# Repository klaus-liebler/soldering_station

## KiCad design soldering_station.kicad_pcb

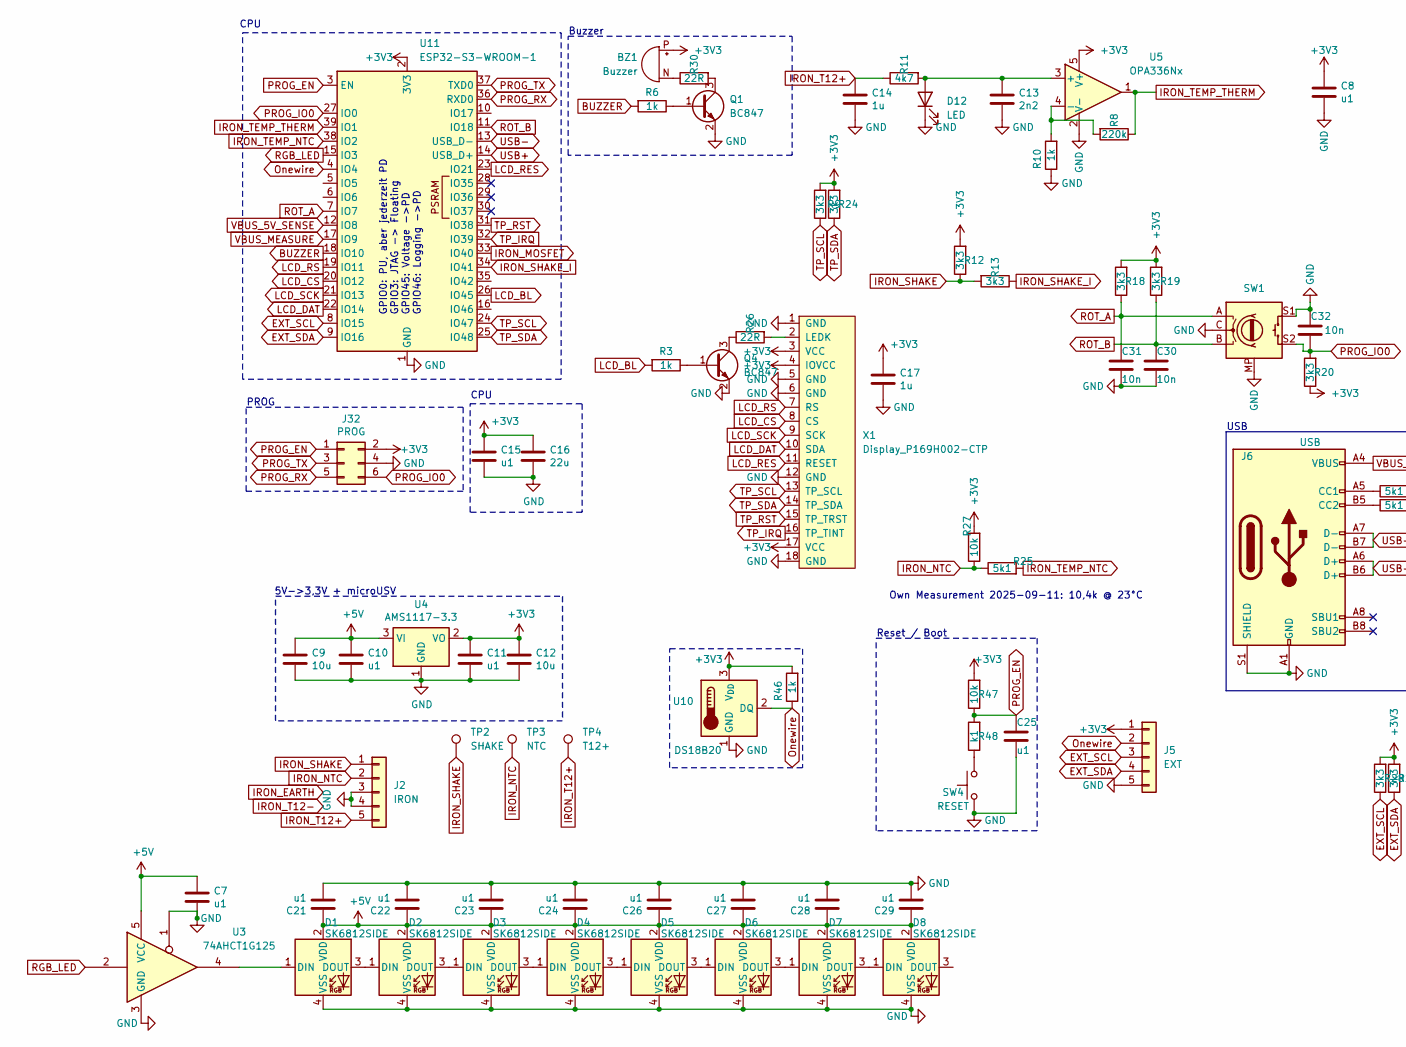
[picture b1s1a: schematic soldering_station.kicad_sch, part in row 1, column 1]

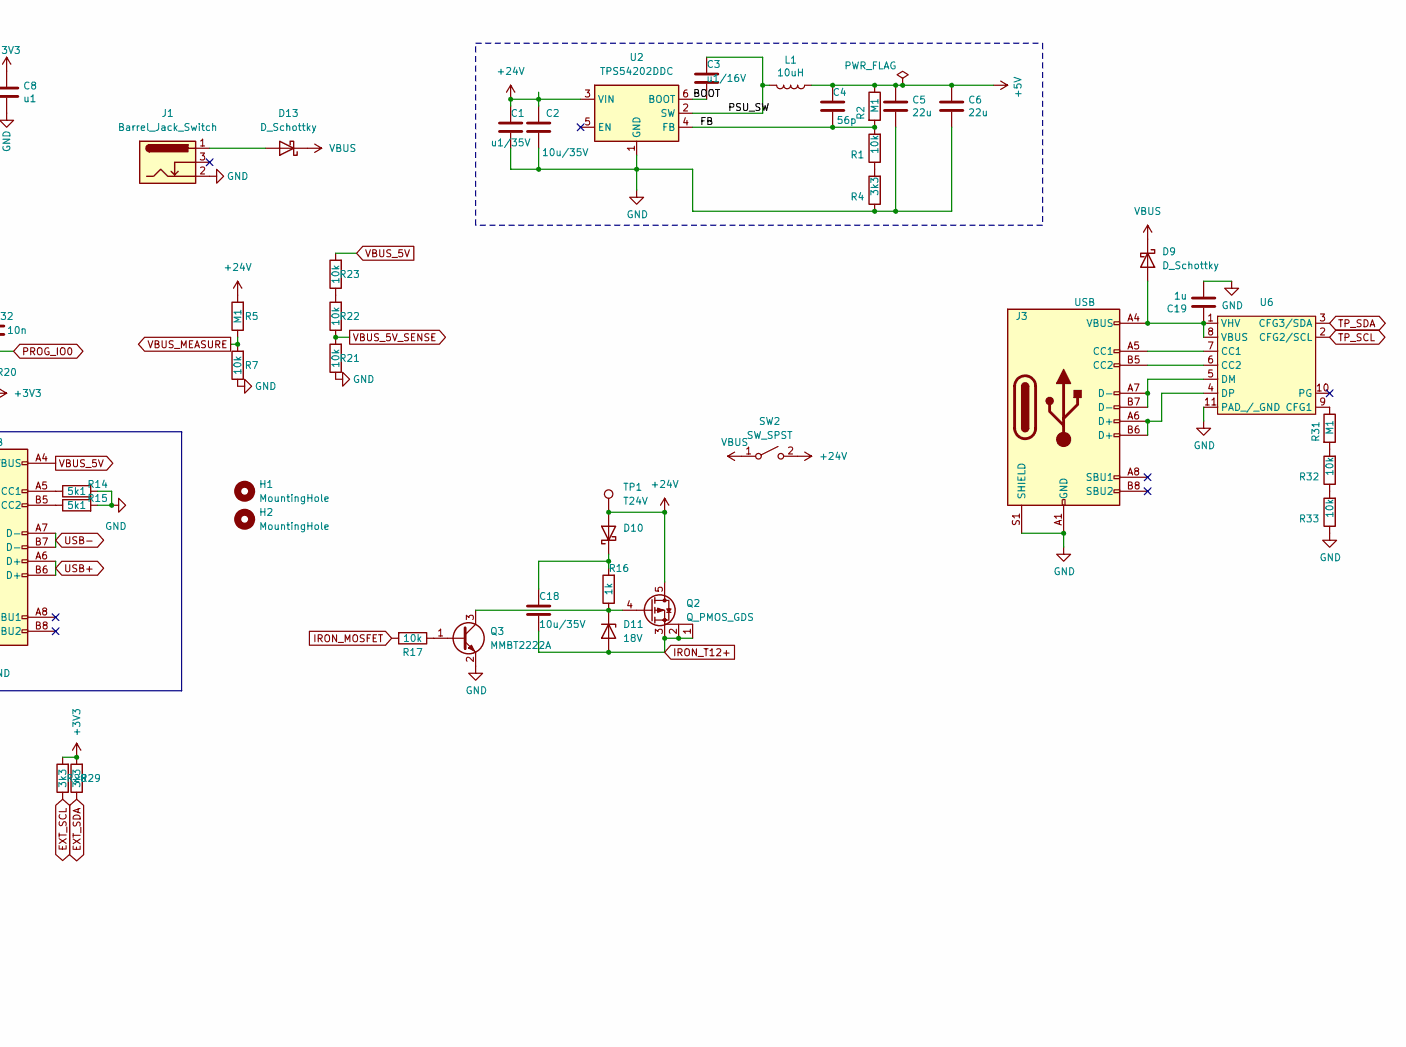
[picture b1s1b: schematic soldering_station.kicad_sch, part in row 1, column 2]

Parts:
BZ1: Buzzer; XDCR_CMT-7525-80-SMT-TR_handsolder
C1: u1/35V; C_0805_2012Metric; MPN CC0603KRX7R9BB104
C2: 10u/35V; C_1206_3216Metric; MPN CGA0805X5R106K350MT
C3: u1/16V; C_0201_0603Metric; MPN CC0603KRX7R9BB104
C4: 56p; C_0201_0603Metric; MPN CC0402JRNPO9BN560
C5, C6: 22u; R_0805_2012Metric_Pad1.20x1.40mm_HandSolder; MPN CL10A226MP8NUNE
C7, C10, C11, C21, C22, C23, C24, C25, C26, C27, C28, C29: u1; C_0201_0603Metric
C8, C15: u1; C_0201_0603Metric; JLCPCB C1525
C9, C12: 10u; C_0603_1608Metric
C13: 2n2; C_0201_0603Metric
C14, C17: 1u; R_0402_1005Metric
C16: 22u; C_0603_1608Metric; JLCPCB C59461
C18: 10u/35V; C_0603_1608Metric
C19: 1u; C_0201_0603Metric
C30, C31, C32: 10n; C_0201_0603Metric
D1, D2, D3, D4, D5, D6, D7, D8: SK6812SIDE; SK6812_SIDE_A
D9, D13: D_Schottky; D_SMA
D10: D_SOD-123_handsolder
D11: 18V; D_SOD-123_handsolder
D12: LED; LED_0805_2012Metric_Pad1.15x1.40mm_HandSolder
H1, H2: MountingHole; MountingHole_3.2mm_M3
J1: Barrel_Jack_Switch; Hohlstecker_vertikal
J2: IRON; GX12-5
J3, J6: USB; GT-USB-7051A
J5: EXT; PinHeader_1x05_P2.54mm_Vertical
J32: PROG; PinHeader_2x03_P1.27mm_Vertical_SMD
L1: 10uH; L_Abracon_ASPI-0630LR; MPN FXL0630-100-M
Q1: BC847; SOT-23
Q2: Q_PMOS_GDS; PQFN-8-EP_6x5mm_P1.27mm_Generic
Q3: MMBT2222A; SOT-23
Q4: BC847; SOT-23_Handsoldering
R1, R32, R33: 10k; R_0201_0603Metric; MPN 0201WMF1002TEE
R2, R31: M1; R_0201_0603Metric; MPN 0201WMF1003TEE
R3, R6, R10: 1k; R_0201_0603Metric
R4: 3k3; R_0201_0603Metric; MPN 0402WGF3301TCE
R5: M1; R_0805_2012Metric_Pad1.20x1.40mm_HandSolder
R7, R17, R21, R22, R23, R27, R47: 10k; R_0201_0603Metric
R8: 220k; R_0201_0603Metric
R9, R12, R13, R18, R19, R20, R24, R28, R29: 3k3; R_0201_0603Metric
R11: 4k7; R_0805_2012Metric_Pad1.20x1.40mm_HandSolder
R14, R15, R25: 5k1; R_0201_0603Metric
R16: 1k; R_0805_2012Metric
R26, R30: 22R; R_0805_2012Metric_Pad1.20x1.40mm_HandSolder
R46: 1k; R_0805_2012Metric_Pad1.20x1.40mm_HandSolder
R48: k1; R_0201_0603Metric
SW1: Rotary_Encoder_Switch_with_Mountingpoint; RotaryEncoder_Alps_EC11E-Switch_Vertical_H20mm
SW2: SW_SPST; KCD1-11-2P
SW4: RESET; Button_2x4x3,5_handsolder
TP1: T24V; TestPoint_THTPad_D1.5mm_Drill0.7mm
TP2: SHAKE; TestPoint_THTPad_D1.5mm_Drill0.7mm
TP3: NTC; TestPoint_THTPad_D1.5mm_Drill0.7mm
TP4: T12+; TestPoint_THTPad_D1.5mm_Drill0.7mm
U2: TPS54202DDC; SOT-23-6_Handsoldering; MPN TPS54202DDCR
U3: 74AHCT1G125; SOT-353_SC-70-5_Handsoldering
U4: AMS1117-3.3; SOT-223-3_TabPin2_HANDSOLDER
U5: OPA336Nx; SOT-23-5
U6: Texas_DSQ0010A_WSON-10-1EP_2x2mm_P0.4mm_EP0.9x1.5mm_Thermal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
U10: DS18B20; TO-92L_HandSolder
U11: ESP32-S3-WROOM-1
X1: Display_P169H002-CTP

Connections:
+3V3: BZ1.P (+), C8.1, C11.1, C12.1, C15.1, C16.1, C17.1, J5.1, J32.2, R9.2, R12.2, R18.2, R19.2, R20.1, R24.2, R27.2, R28.2, R29.2, R46.2, R47.2, U4.2 (VO), U5.5 (V+), U10.3 (V_{DD}), U11.2 (3V3), X1.3 (VCC), X1.4 (IOVCC), X1.17 (VCC)
+5V: C4.2, C5.1, C6.1, C7.1, C9.1, C10.1, C21.1, C22.1, C23.1, C24.1, C26.1, C27.1, C28.1, C29.1, D1.2 (VDD), D2.2 (VDD), D3.2 (VDD), D4.2 (VDD), D5.2 (VDD), D6.2 (VDD), D7.2 (VDD), D8.2 (VDD), L1.1, R2.1, U3.5 (VCC), U4.3 (VI)
+24V: C1.2, C2.2, D10.2 (A), Q2.5 (D), R5.2, SW2.2 (B), TP1.1, U2.3 (VIN)
/BOOT: C3.1, U2.6 (BOOT)
/FB: C4.1, R1.2, R2.2, U2.4 (FB)
/PSU_SW: C3.2, L1.2, U2.2 (SW)
BUZZER: R6.2, U11.18 (IO10)
EXT_SCL: J5.3, R28.1, U11.8 (IO15)
EXT_SDA: J5.4, R29.1, U11.9 (IO16)
GND: C1.1, C2.1, C5.2, C6.2, C7.2, C8.2, C9.2, C10.2, C11.2, C12.2, C13.2, C14.2, C15.2, C16.2, C17.2, C19.2, C21.2, C22.2, C23.2, C24.2, C25.2, C26.2, C27.2, C28.2, C29.2, C30.2, C31.2, C32.1, D1.4 (VSS), D2.4 (VSS), D3.4 (VSS), D4.4 (VSS), D5.4 (VSS), D6.4 (VSS), D7.4 (VSS), D8.4 (VSS), D12.1 (K), J1.2, J2.3, J2.4, J3.A1 (GND), J3.A12 (GND), J3.B1 (GND), J3.B12 (GND), J3.S1 (SHIELD), J5.5, J6.A1 (GND), J6.A12 (GND), J6.B1 (GND), J6.B12 (GND), J6.S1 (SHIELD), J32.4, Q1.2 (E), Q3.2 (E), Q4.2 (E), R4.1, R7.1, R10.1, R14.2, R15.2, R21.1, R33.1, SW1.C, SW1.MP, SW1.S1, SW4.2, U2.1 (GND), U3.1, U3.3 (GND), U4.1 (GND), U5.2 (V-), U6.11 (PAD_/_GND), U10.1 (GND), U11.1 (GND), U11.40 (GND), U11.41 (GND), X1.1 (GND), X1.5 (GND), X1.6 (GND), X1.12 (GND), X1.18 (GND)
IRON_MOSFET: R17.2, U11.33 (IO40)
IRON_NTC: J2.2, R25.1, R27.1, TP3.1
IRON_SHAKE: J2.1, R12.1, R13.2, TP2.1
IRON_SHAKE_I: R13.1, U11.34 (IO41)
IRON_T12+: C14.1, C18.2, D11.2 (A), J2.5, Q2.1 (S), Q2.2 (S), Q2.3 (S), R11.1, TP4.1
IRON_TEMP_NTC: R25.2, U11.38 (IO2)
IRON_TEMP_THERM: R8.1, U5.1, U11.39 (IO1)
LCD_BL: R3.2, U11.26 (IO45)
LCD_CS: U11.20 (IO12), X1.8 (CS)
LCD_DAT: U11.22 (IO14), X1.10 (SDA)
LCD_RES: U11.23 (IO21), X1.11 (RESET)
LCD_RS: U11.19 (IO11), X1.7 (RS)
LCD_SCK: U11.21 (IO13), X1.9 (SCK)
unnamed: BZ1.N (-), R30.1
unnamed: D1.1 (DIN), U3.4
unnamed: D1.3 (DOUT), D2.1 (DIN)
unnamed: D2.3 (DOUT), D3.1 (DIN)
unnamed: D3.3 (DOUT), D4.1 (DIN)
unnamed: D4.3 (DOUT), D5.1 (DIN)
unnamed: D5.3 (DOUT), D6.1 (DIN)
unnamed: D6.3 (DOUT), D7.1 (DIN)
unnamed: D7.3 (DOUT), D8.1 (DIN)
unnamed: C19.1, D9.2 (A), J3.A4 (VBUS), J3.A9 (VBUS), J3.B4 (VBUS), J3.B9 (VBUS), U6.1 (VHV), U6.8 (VBUS)
unnamed: C18.1, D10.1 (K), R16.2
unnamed: D11.1 (K), Q2.4 (G), Q3.3 (C), R16.1
unnamed: C13.1, D12.2 (A), R11.2, U5.3 (+)
unnamed: D13.2 (A), J1.1
unnamed: J3.A5 (CC1), U6.7 (CC1)
unnamed: J3.B5 (CC2), U6.6 (CC2)
unnamed: J6.A5 (CC1), R14.1
unnamed: J6.B5 (CC2), R15.1
unnamed: Q1.1 (B), R6.1
unnamed: Q1.3 (C), R30.2
unnamed: Q3.1 (B), R17.1
unnamed: Q4.1 (B), R3.1
unnamed: Q4.3 (C), R26.1
unnamed: R1.1, R4.2
unnamed: R22.2, R23.1
unnamed: R31.2, R32.2
unnamed: R32.1, R33.2
unnamed: R48.1, SW4.1
unnamed: R8.2, R10.2, U5.4 (-)
unnamed: R31.1, U6.9 (CFG1)
unnamed: J3.A7 (D-), J3.B7 (D-), U6.5 (DM)
unnamed: J3.A6 (D+), J3.B6 (D+), U6.4 (DP)
unnamed: R26.2, X1.2 (LEDK)
Onewire: J5.2, R46.1, U10.2 (DQ), U11.4 (IO4)
PROG_EN: C25.1, J32.1, R47.1, R48.2, U11.3 (EN)
PROG_IO0: C32.2, J32.6, R20.2, SW1.S2, U11.27 (IO0)
PROG_RX: J32.5, U11.36 (RXD0)
PROG_TX: J32.3, U11.37 (TXD0)
RGB_LED: U3.2, U11.15 (IO3)
ROT_A: C31.1, R18.1, SW1.A, U11.7 (IO7)
ROT_B: C30.1, R19.1, SW1.B, U11.11 (IO18)
TP_IRQ: U11.32 (IO39), X1.16 (TP_TINT)
TP_RST: U11.31 (IO38), X1.15 (TP_TRST)
TP_SCL: R9.1, U6.2 (CFG2/SCL), U11.24 (IO47), X1.13 (TP_SCL)
TP_SDA: R24.1, U6.3 (CFG3/SDA), U11.25 (IO48), X1.14 (TP_SDA)
USB+: J6.A6 (D+), J6.B6 (D+), U11.14 (USB_D+)
USB-: J6.A7 (D-), J6.B7 (D-), U11.13 (USB_D-)
VBUS: D9.1 (K), D13.1 (K), SW2.1 (A)
VBUS_5V: J6.A4 (VBUS), J6.A9 (VBUS), J6.B4 (VBUS), J6.B9 (VBUS), R23.2
VBUS_5V_SENSE: R21.2, R22.1, U11.12 (IO8)
VBUS_MEASURE: R5.1, R7.2, U11.17 (IO9)

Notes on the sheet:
Own Measurement 2025-09-11: 10,4k @ 23°C
CPU
5V->3,3V + microUSV
GPIO0: PU, aber jederzeit PD GPIO3: JTAG -> Floating GPIO45: Voltage ->PD GPIO46: Logging ->PD
PROG
Buzzer
USB
Reset / Boot

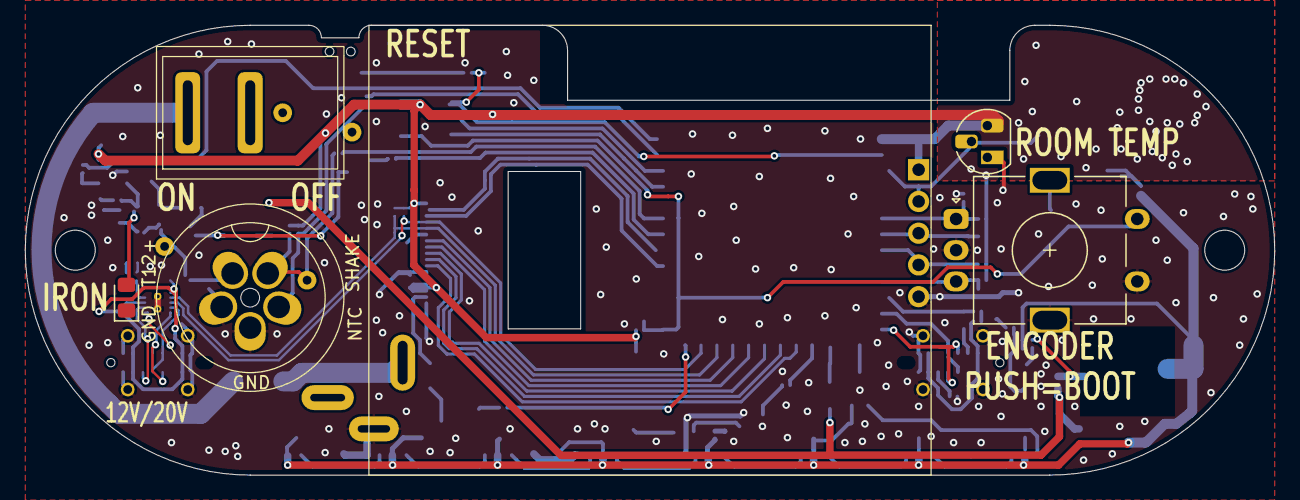
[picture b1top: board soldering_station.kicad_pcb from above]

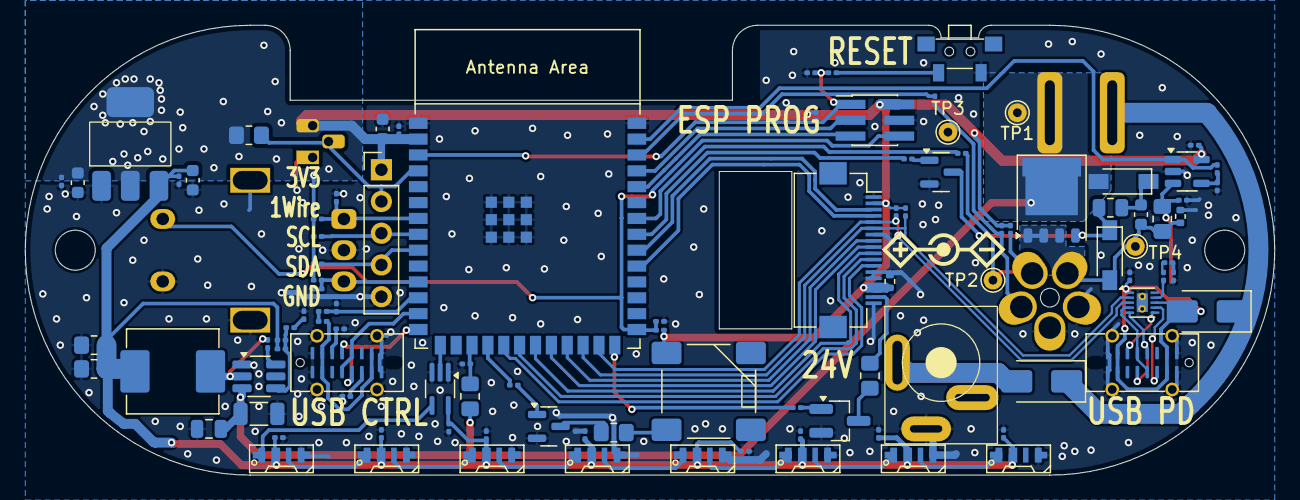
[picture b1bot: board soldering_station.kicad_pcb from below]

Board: 2 copper layers, 100.0 x 36.0 mm, 109 parts (102 on the bottom side), 74 nets.

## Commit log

2025-09-11 Ready for review
2025-09-29 Various Updates
2025-10-02 spice simulation for power stage
2025-12-01 spice models
2026-02-24 Layout improvements
